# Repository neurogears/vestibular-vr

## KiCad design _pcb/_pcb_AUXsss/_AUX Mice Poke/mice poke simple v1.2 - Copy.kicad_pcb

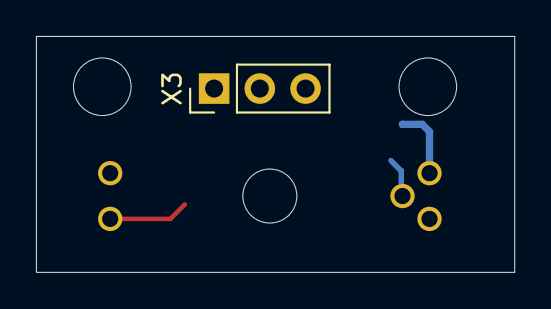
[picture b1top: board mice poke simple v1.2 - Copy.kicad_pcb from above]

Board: 2 copper layers, 26.6 x 13.1 mm, 5 parts (1 on the bottom side), 2 nets.

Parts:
@HOLE0, @HOLE1, @HOLE2: (no value)
U1: Val**; GP1A57HR_CUT2
X3: PinHeader_1x03_P2.54mm_Vertical

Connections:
+5V: U1.3, X3.1
GND: U1.2, U1.5, X3.2

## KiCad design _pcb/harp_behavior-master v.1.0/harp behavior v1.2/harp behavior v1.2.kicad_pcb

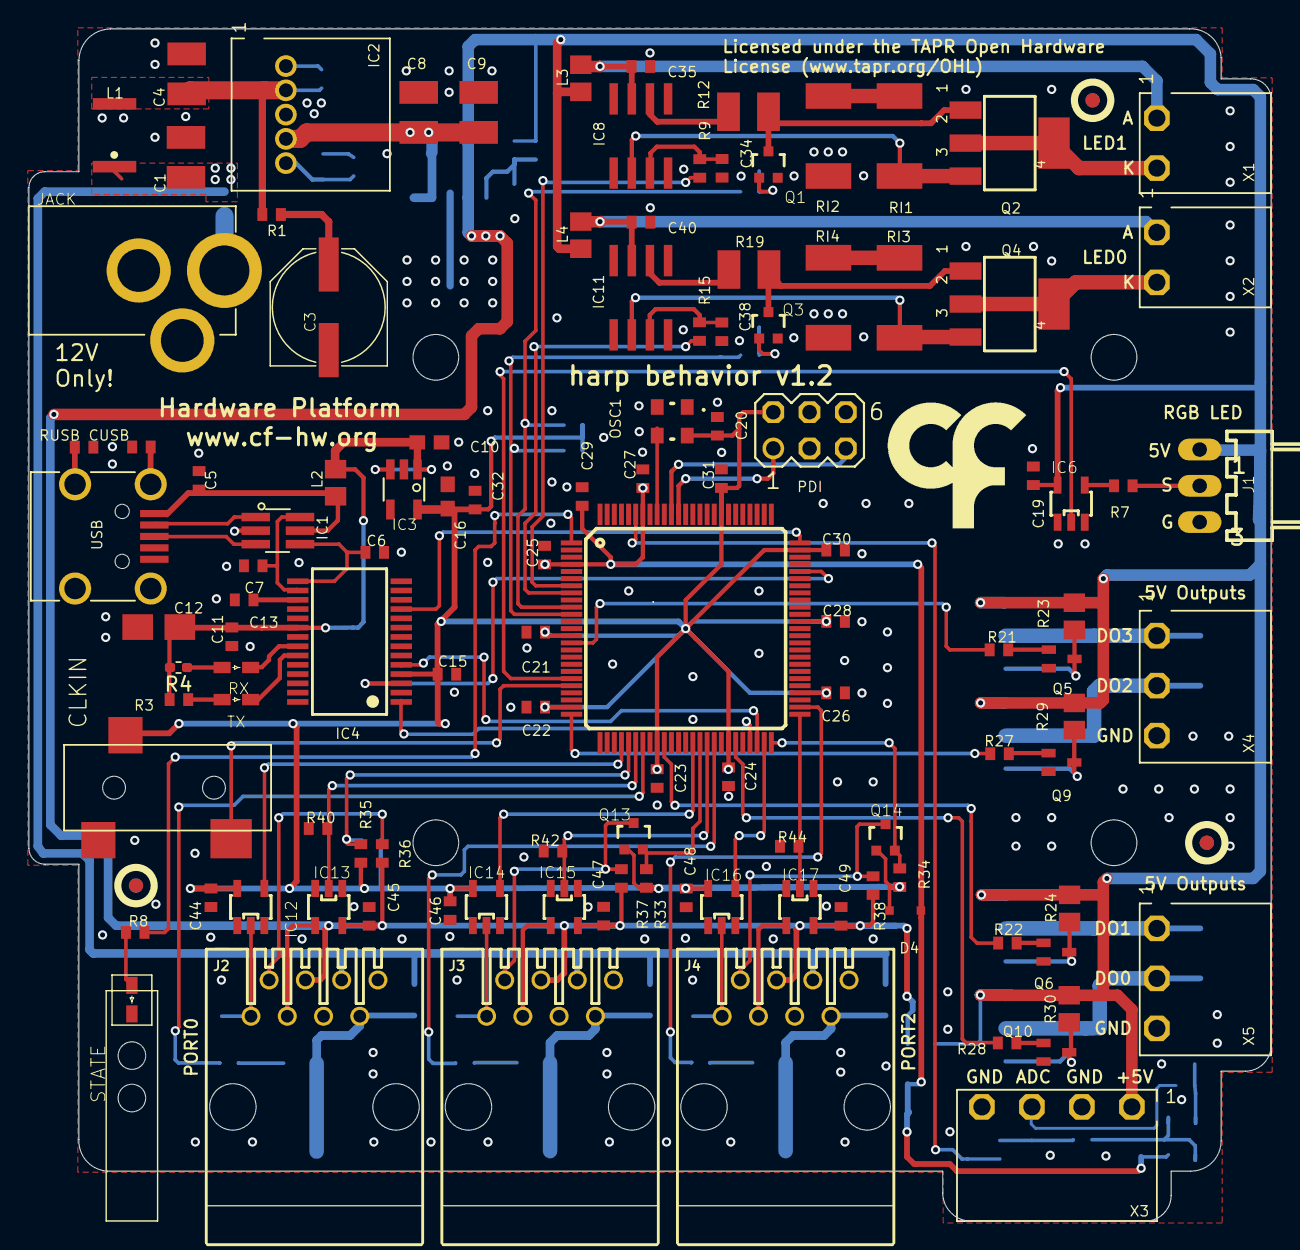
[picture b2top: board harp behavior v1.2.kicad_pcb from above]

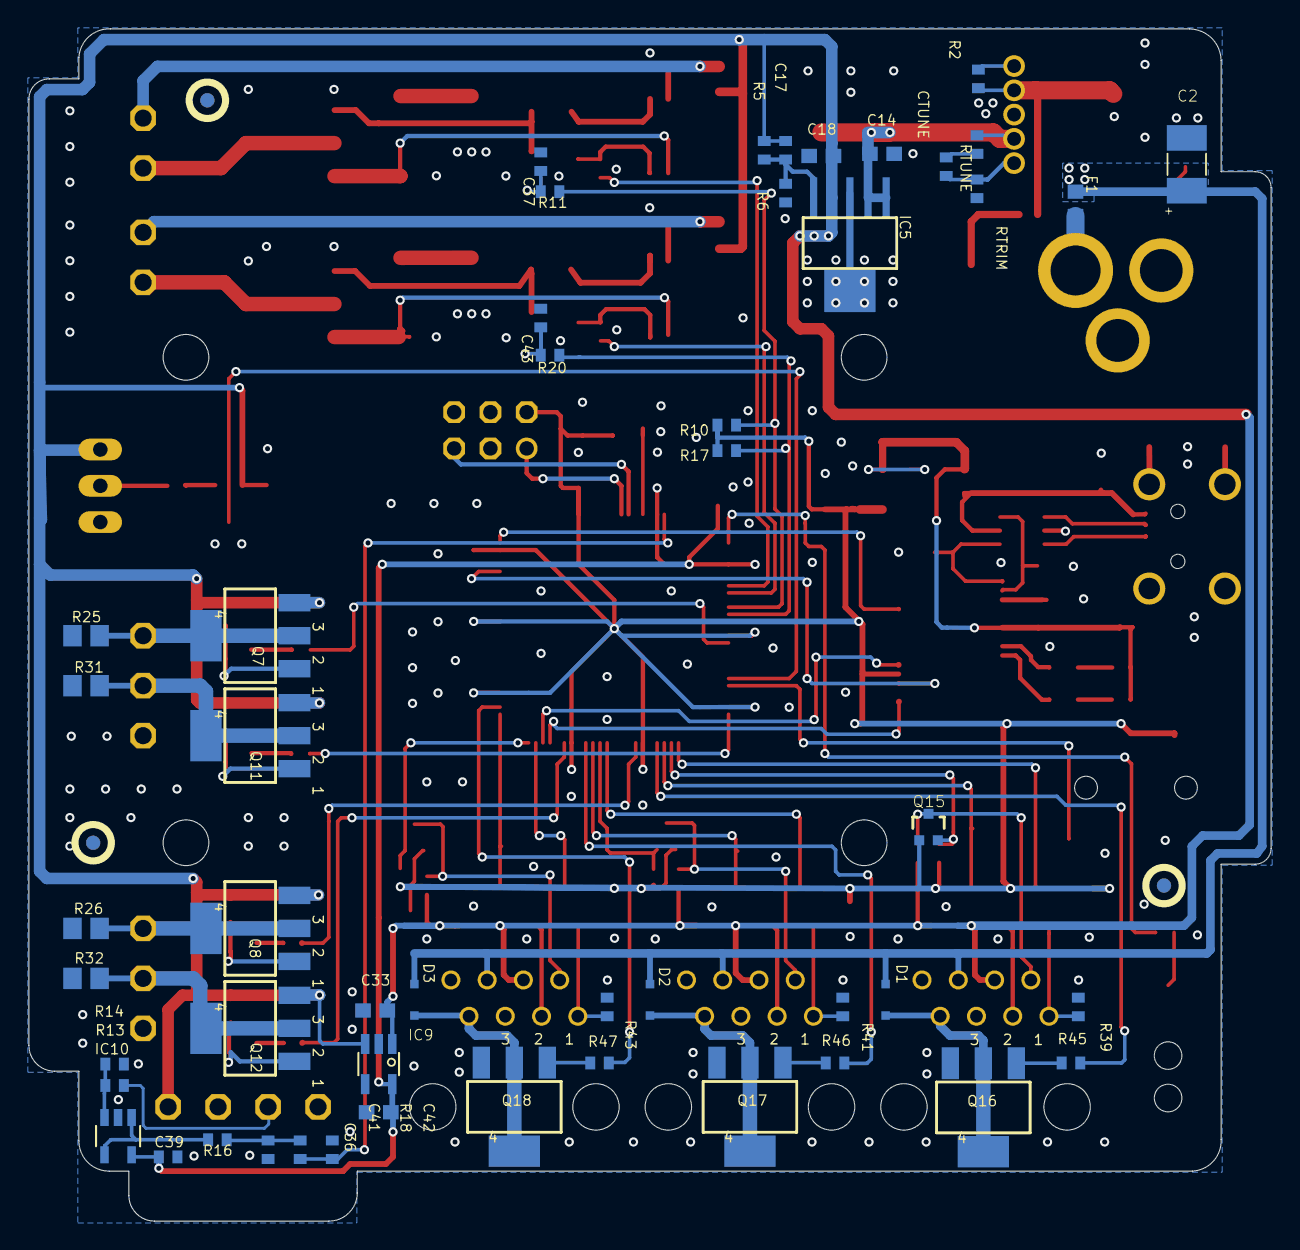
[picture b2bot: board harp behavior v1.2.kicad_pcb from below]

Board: 4 copper layers, 87.0 x 83.5 mm, 178 parts (53 on the bottom side), 107 nets.

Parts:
@HOLE0, @HOLE1, @HOLE2, @HOLE3: (no value)
C1, C4: 22uF; C1210
C2: 22uF; CAP_100UF_HAND
C3: 100uF; PANASONIC_E
C5, C11, C13, C15, C19, C20, C21, C22, C23, C24, C25, C26, C27, C28, C30, C31, C35, C37, C39, C40, C43, C44, C45, C46, C47, C48, C49: 100nF; C0402
C6, C7: 47pF; C0402
C8, C9: 47uF; C1210
C10, C14, C16, C18, C33, C36: 10uF; C0603
C12: 4.7uF; A_3216-18W
C17: 13pF; C0402
C29, C32: 330nF; C0402
C34, C38: NA; C0402
C41, C42: 15nF 5%; C0402
CLKIN: 35RASMT2BHNTRX
CTUNE: NA; C0402
CUSB: 4.7nF; C0402
D1, D2, D3, D4: NA; SOD323-R
F1: 1A FB; R0603
IC1: USBLC6-2SC6; SOT23-6L
IC2: DC-DC-SIP-5; SIP-5
IC3, IC9: LP5907MFX-3.3; TSOT23-5
IC4: FT232RL; SSOP28
IC5: TPS78630DCQ; SOT223-6
IC6, IC13, IC15, IC17: M74VHC1GT50DTT1G; SOT23-5
IC7: XMEGA-A1TQFP; TQFP100
IC8, IC11: SO8
IC10: OPA365; SOT23-5
IC12, IC14, IC16: SN74LVC1G125; SOT23-5
J1: 22-05-7038-03; 7395-03
J2: Port 0; 520426-4
J3: Port 1; 520426-4
J4: Port 2; 520426-4
JACK: DC_JACK2.1MM; DC_POWER_INPUT_2.1MM
L1: 1.5u; IND_LPS4012
L2: ???; R0805
L3, L4: 600@100M; R0805
OSC1: OSCILLATOR_3.2X2.5
PDI: MA03-2
Q1, Q3, Q13, Q14, Q15: MOSFET-NCHANNELSOT323; SOT323
Q2, Q4, Q7, Q8, Q11, Q12, Q16, Q17, Q18: SOT223
Q5, Q6, Q9, Q10: BC817-40W; SOT323-BEC
R1, R9, R15: 0; R0402
R2: NA; R0402
R3: 2050 NA; R0402
R4: 680 NA; R_0402_1005Metric_Pad0.72x0.64mm_HandSolder
R5: 95.3k; R0402
R6: 30.9k; R0402
R7, R11, R20: 100; R0402
R8: 68; R0402
R10, R17, R39, R40, R41, R42, R43, R44: 100k; R0402
R12, R19: 200; R1210
R13: 24k; R0402
R14: 16k; R0402
R16, R18: 10k 1%; R0402
R21, R22, R27, R28, R33, R34, R35, R36, R37, R38: 10k; R0402
R23, R24, R25, R26, R29, R30, R31, R32: 549; R0805
R45, R46, R47: 330; R0402
RI1, RI2, RI3, RI4: 4.99; R2512
RTRIM: 243; R0402
RTUNE: NA; R0402
RUSB: 1M; R0402
RX: GREEN NA; LED_HAND
STATE: GREEN; LED_HAND
TX: RED NA; LED_HAND
U$1: LED_PIPE_7513D2-L
U$2, U$3, U$4, U$5, U$6, U$7: FIDUCIAL
U$9: LOGO_6
USB: 240-0002-1
X1, X2: CON_3.5MM_1X2
X3: CON_3.5MM_1X4
X4, X5: CON_3.5MM_1X3

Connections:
5V_RAW: C10.1, C11.1, C12.+, IC3.1, IC3.3, IC4.20, L2.1, R3.2, R4.2
+5V: C17.1, C18.1, C19.1, C33.1, C45.1, C47.1, C49.1, IC5.P$4, IC6.5, IC9.1, IC9.3, IC13.5, IC15.5, IC17.5, J1.1, J2.4, J3.4, J4.4, L3.1, L4.1, Q7.3, Q8.3, Q11.3, Q12.3, R5.2, R23.1, R24.1, R29.1, R30.1, R36.1, R37.1, R38.1, X3.P1
+12V: C1.1, C2.+, D1.C, D2.C, D3.C, F1.1, J2.6, J3.6, J4.6, L1.1
ADC0: C42.2, IC7.95, R18.2
ADC0_IN: R13.2, X3.P3
CLK_IN: CLKIN.4, IC7.21
CTRL_BL: IC11.6, R19.1
CTRL_BL1: IC8.6, R12.1
C_M0: IC8.2, Q2.3, RI1.2
C_M1: IC11.2, Q4.3, RI3.2
DAC0: IC7.8, R15.1
DAC1: IC7.7, R9.1
DCIN: C4.1, IC2.P2, L1.2, R1.2, R2.2
DIO_PK0: J2.2, Q15.3, R36.2
DIO_PK1: J3.2, Q13.3, R37.2
DIO_PK2: J4.2, Q14.3, R38.2
DI_PK0: IC12.2, J2.1, R39.1
DI_PK1: IC14.2, J3.1, R41.1
DI_PK2: IC16.2, J4.1, R43.1
DO0: Q12.2, Q12.4, R32.2, X5.P2
DO1: Q8.2, Q8.4, R26.2, X5.P1
DO2: Q11.2, Q11.4, R31.2, X4.P2
DO3: Q7.2, Q7.4, R25.2, X4.P1
DO_PK0: IC13.4, J2.3
DO_PK1: IC15.4, J3.3
DO_PK2: IC17.4, J4.3
FT_CTS: IC4.11, IC7.75
FT_RTS: IC4.3, IC7.71
FT_RXD: IC4.5, IC7.48
FT_TXD: IC4.1, IC7.47
GND: C1.2, C2.-, C3.-, C4.2, C5.2, C6.2, C7.2, C8.2, C9.2, C10.2, C11.2, C12.-, C13.2, C14.2, C15.2, C16.2, C18.2, C19.2, C20.2, C21.2, C22.2, C23.2, C24.2, C25.2, C26.2, C27.2, C28.2, C29.2, C30.2, C31.2, C32.2, C33.2, C34.2, C35.2, C36.2, C37.2, C38.2, C39.2, C40.2, C41.1, C42.1, C43.2, C44.2, C45.2, C46.2, C47.2, C48.2, C49.2, CLKIN.5, CUSB.2, IC1.P$2, IC2.P3, IC3.2, IC4.7, IC4.18, IC4.21, IC4.25, IC4.26, IC5.P$3, IC5.P$6, IC6.1, IC6.3, IC7.3, IC7.13, IC7.23, IC7.33, IC7.43, IC7.53, IC7.63, IC7.73, IC7.84, IC7.93, IC7.96, IC8.4, IC9.2, IC10.2, IC11.4, IC12.1, IC12.3, IC13.1, IC13.3, IC14.1, IC14.3, IC15.1, IC15.3, IC16.1, IC16.3, IC17.1, IC17.3, J1.3, J2.5, J3.5, J4.5, JACK.P2, JACK.P3, OSC1.P$2, PDI.6, Q1.2, Q3.2, Q5.E, Q6.E, Q9.E, Q10.E, Q16.3, Q17.3, Q18.3, R6.1, R14.1, R25.1, R26.1, R31.1, R32.1, R39.2, R40.1, R41.2, R42.1, R43.2, R44.2, RI2.1, RI4.1, RTRIM.1, RUSB.2, STATE.K, USB.P$5, X3.P2, X3.P4, X4.P3, X5.P3
I_OFF_DAC0: IC7.11, R17.2, R20.1
I_OFF_DAC1: IC7.10, R10.2, R11.1
LED_5V_0: C35.1, IC8.7, L3.2, X1.P1
LED_5V_1: C40.1, IC11.7, L4.2, X2.P1
LED_DATA: IC6.2, IC7.20
LED_RTN0: Q2.2, Q2.4, X1.P2
LED_RTN1: Q4.2, Q4.4, X2.P2
unnamed: Q3.3, Q4.1, R19.2
unnamed: Q16.1, R45.2
unnamed: Q6.C, Q8.1, R24.2
unnamed: Q17.1, R46.2
unnamed: Q6.B, R22.2
unnamed: Q18.1, R47.2
unnamed: Q9.C, Q11.1, R29.2
unnamed: Q9.B, R27.2
unnamed: Q10.C, Q12.1, R30.2
unnamed: Q10.B, R28.2
unnamed: Q1.3, Q2.1, R12.2
unnamed: CTUNE.2, IC2.P5, RTRIM.2
unnamed: IC6.4, R7.2
unnamed: CTUNE.1, RTUNE.1
unnamed: C34.1, IC8.3, R9.2
unnamed: IC2.P1, R2.1
unnamed: F1.2, JACK.P1
unnamed: C17.2, IC5.P$5, R5.1, R6.2
unnamed: C38.1, IC11.3, R15.2
unnamed: RI1.1, RI2.2
unnamed: R8.1, STATE.A
unnamed: C3.+, R1.1
unnamed: Q5.C, Q7.1, R23.2
unnamed: Q5.B, R21.2
unnamed: C37.1, Q1.1, R11.2
unnamed: C43.1, Q3.1, R20.2
unnamed: C13.1, IC4.17
unnamed: C5.1, IC1.P$5, L2.2, USB.P$1
unnamed: IC1.P$1, USB.P$2
unnamed: RI3.1, RI4.2
unnamed: R4.1, RX.A
unnamed: IC4.23, TX.K
unnamed: IC4.22, RX.K
unnamed: IC1.P$3, USB.P$3
unnamed: C41.2, R16.2, R18.1
unnamed: IC10.1, IC10.4, R16.1
unnamed: CUSB.1, USB.SHIELD_4
unnamed: RUSB.1, USB.SHIELD_1
unnamed: R3.1, TX.A
unnamed: IC10.3, R13.1, R14.2
OSC1: IC7.92, OSC1.P$3
P5.45V: C8.1, C9.1, C14.1, IC2.P4, IC5.P$1, IC5.P$2, RTUNE.2
PDI-CLK: IC7.90, PDI.5
PDI-DATA: IC7.89, PDI.1
PK0_IN: IC7.29, IC12.4
PK0_IO: IC7.30, Q15.2, R35.2
PK0_OUT: IC7.31, IC13.2, R40.2
PK0_VAL: IC7.32, R45.1
PK1_IN: IC7.39, IC14.4
PK1_IO: IC7.40, Q13.2, R33.2
PK1_OUT: IC7.41, IC15.2, R42.2
PK1_VAL: IC7.42, R46.1
PK2_IN: IC7.49, IC16.4
PK2_IO: IC7.50, Q14.2, R34.2
PK2_OUT: IC7.51, IC17.2, R44.1
PK2_VAL: IC7.52, R47.1
SERIAL_LED0: J1.2, R7.1
STATE: IC7.1, R8.2
TOG_D00: IC7.45, R28.1
TOG_D01: IC7.35, R22.1
TOG_D02: IC7.25, R27.1
TOG_D03: IC7.15, R21.1
USBDM: C7.1, IC1.P$6, IC4.16
USBDP: C6.1, IC1.P$4, IC4.15
VAL_PK0: D1.A, J2.7, Q16.2, Q16.4
VAL_PK1: D2.A, J3.7, Q17.2, Q17.4
VAL_PK2: D3.A, J4.7, Q18.2, Q18.4
VCCIO: C15.1, C16.1, C20.1, C21.1, C22.1, C23.1, C24.1, C26.1, C28.1, C30.1, C31.1, C32.1, C44.1, C46.1, C48.1, CLKIN.1, D4.A, IC3.5, IC4.4, IC7.14, IC7.24, IC7.34, IC7.44, IC7.54, IC7.64, IC7.74, IC7.83, IC12.5, IC14.5, IC16.5, OSC1.P$4, PDI.2, Q13.1, Q14.1, Q15.1, R10.1, R17.1, R33.1, R34.1, R35.1
VDD: C25.1, C27.1, C29.1, C36.1, C39.1, D4.C, IC7.4, IC7.94, IC9.5, IC10.5

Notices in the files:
_pcb/harp_behavior-master v.1.0/harp behavior v1.2/harp behavior v1.2.kicad_pcb:
Licensed under the TAPR Open
Hardware License (www.tapr.org/OHL)
Copyright 2017 Artur Silva and Filipe Carvalho
Licensed under the TAPR Open Hardware
